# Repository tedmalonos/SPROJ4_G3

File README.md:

# **02-d plotter PCB 4-layer**
<br />
Front view<br />
<br />
Back view<br />
<br />

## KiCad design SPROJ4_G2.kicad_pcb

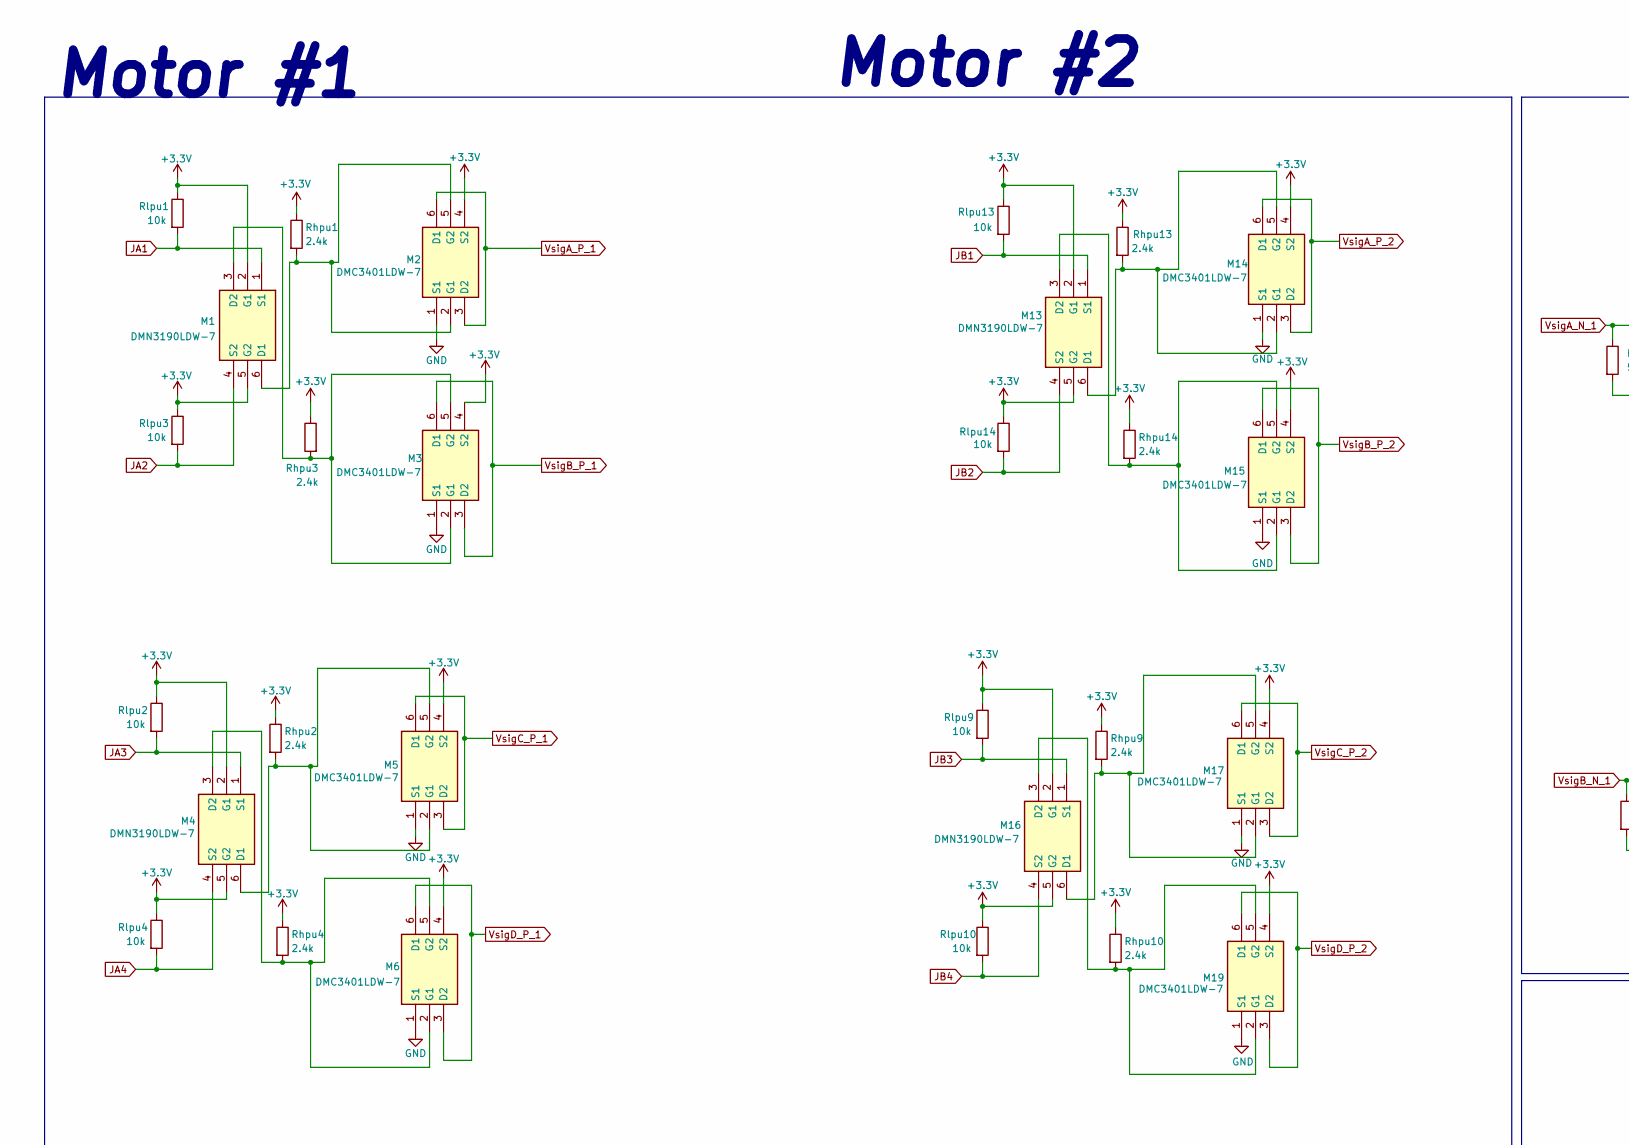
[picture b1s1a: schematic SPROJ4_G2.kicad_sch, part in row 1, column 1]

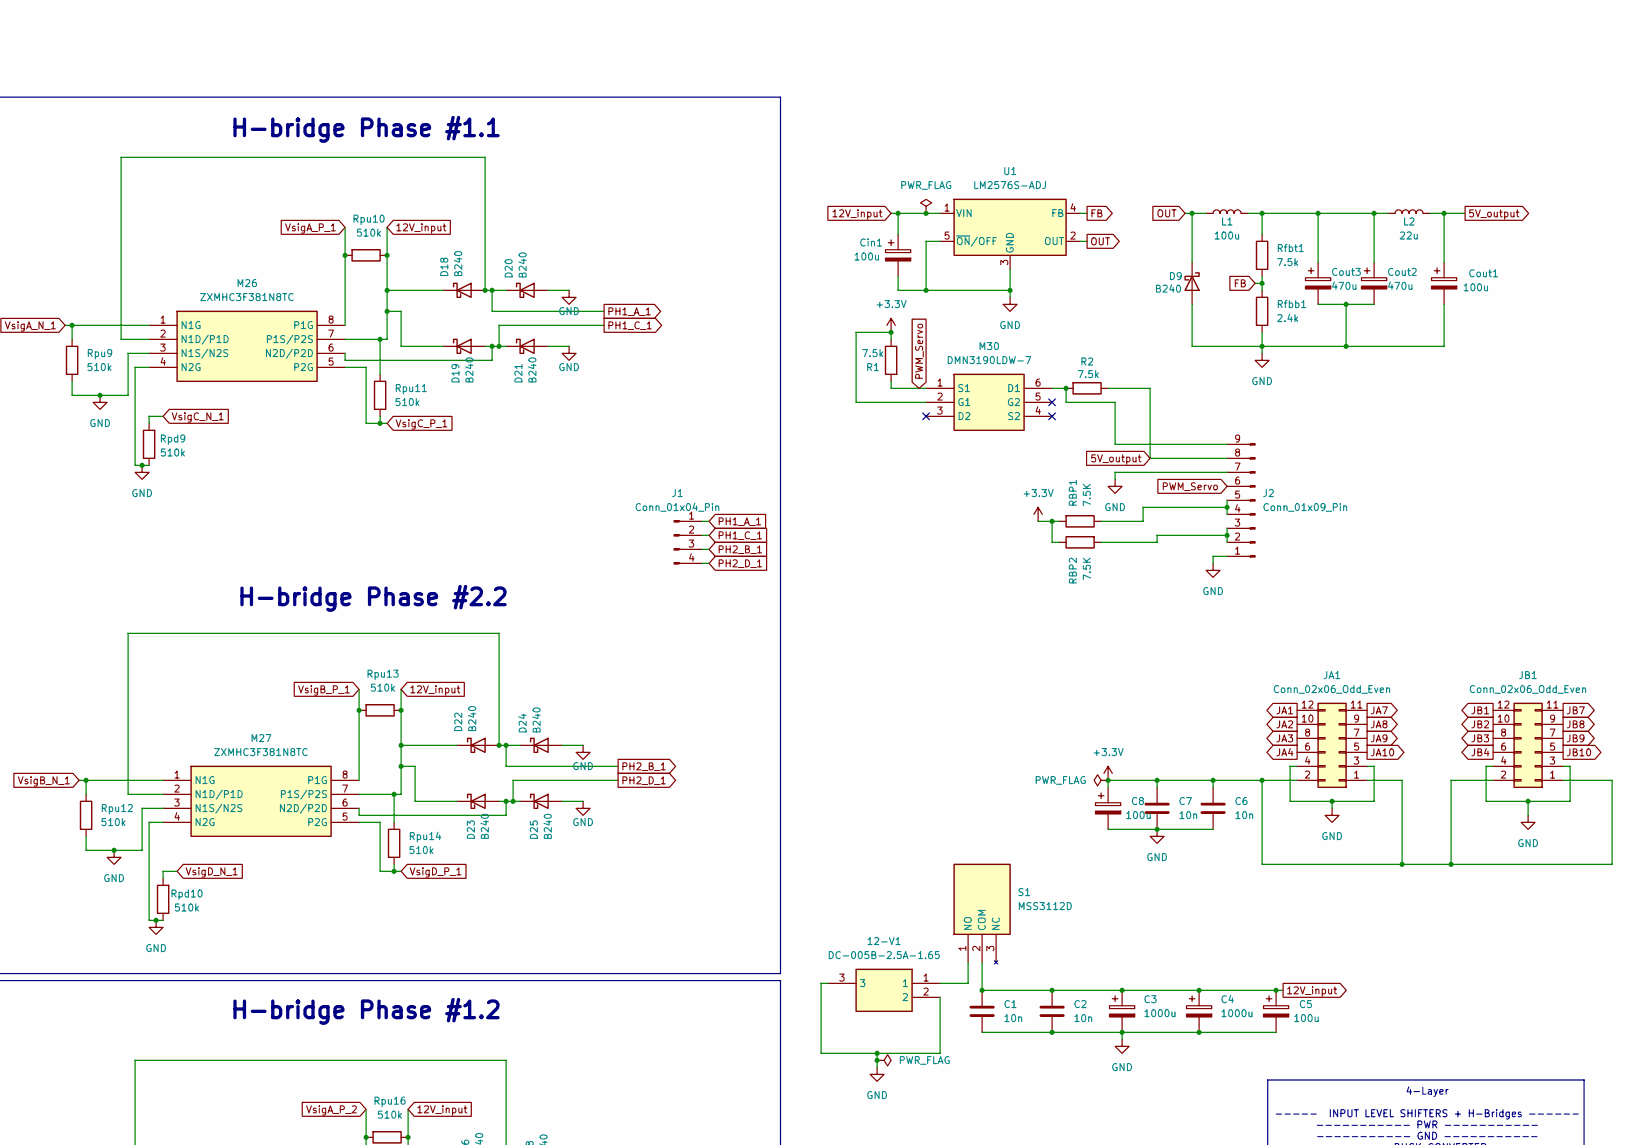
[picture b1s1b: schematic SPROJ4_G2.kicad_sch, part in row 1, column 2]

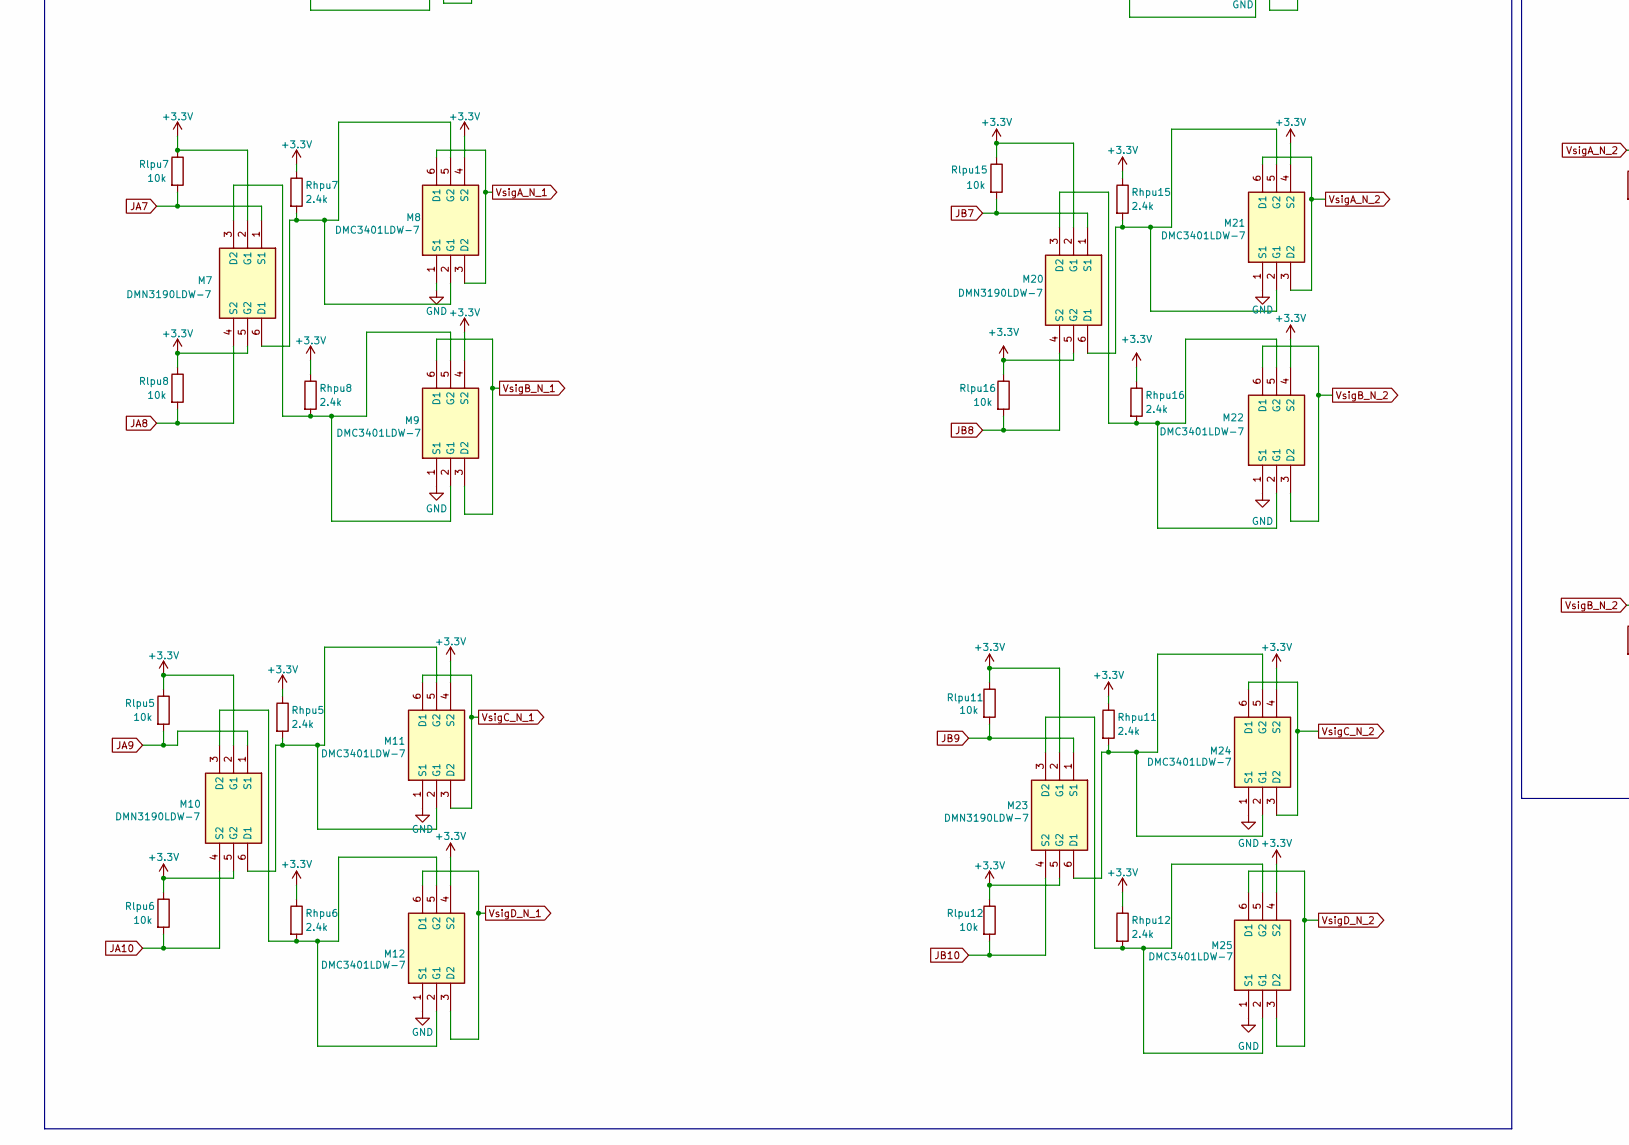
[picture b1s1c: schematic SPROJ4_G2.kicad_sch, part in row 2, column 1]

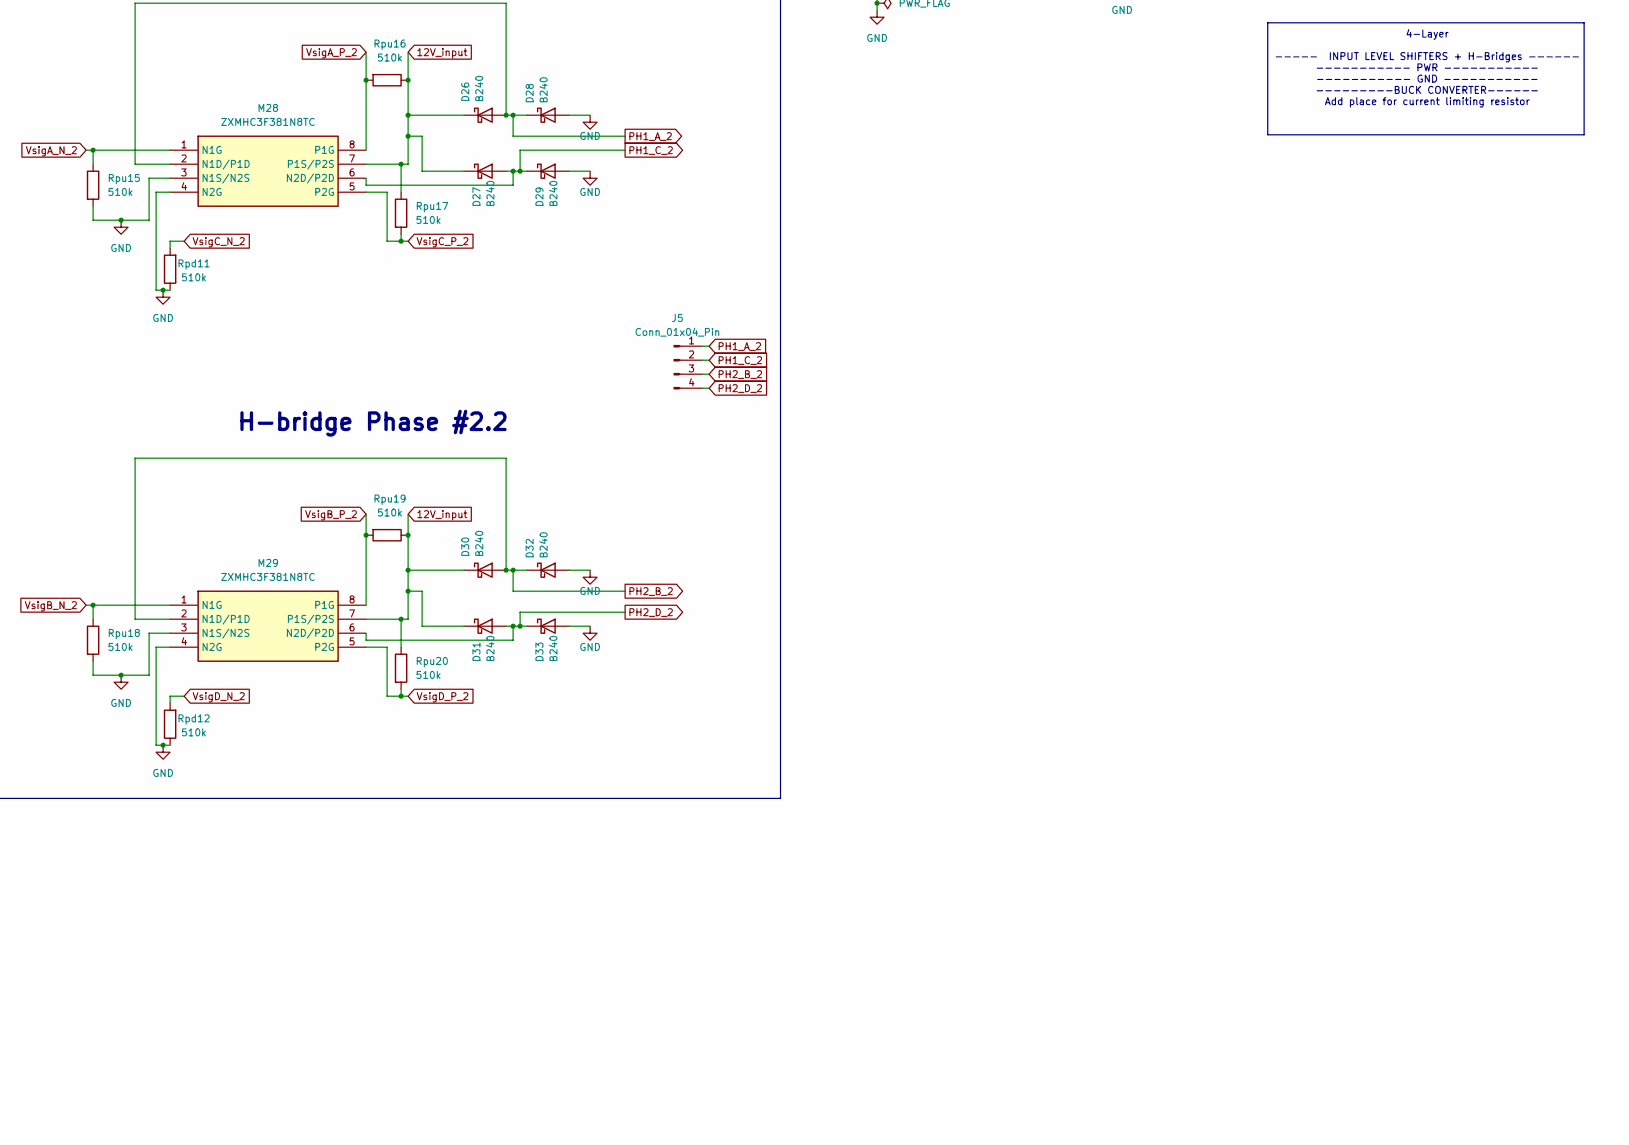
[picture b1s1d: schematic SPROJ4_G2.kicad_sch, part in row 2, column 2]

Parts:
12-V1: DC-005B-2.5A-1.65; DC005B25A165; Manufacturer_Part_Number DC-005B-2.5A-1.65
C1, C2, C6, C7: 10n; C_0805_2012Metric_Pad1.18x1.45mm_HandSolder
C3, C4: 1000u; EEE0JA152UAP_1
C5, C8: 100u; EEE1AA101SP
Cin1: 100u; EEE1AA101SP
Cout1: 100u; EEE1AA101SP
Cout2, Cout3: 470u; EEHZT1E331UP
D9: B240; D_SMA-SMB_Universal_Handsoldering
D18, D19, D20, D21, D22, D23, D24, D25, D26, D27, D28, D29, D30, D31, D32, D33: B240; D_SMB
J1, J5: Conn_01x04_Pin; JST_EH_B4B-EH-A_1x04_P2.50mm_Vertical
J2: Conn_01x09_Pin; PinHeader_1x09_P2.54mm_Horizontal
JA1: Conn_02x06_Odd_Even; PinHeader_2x06_P2.54mm_Horizontal
JB1: Conn_02x06_Odd_Even; PinHeader_2x06_P2.54mm_Horizontal
L1: 100u; SDR2207101KL
L2: 22u; L_Bourns_SRN6045TA
M1, M4, M7, M10, M13, M16, M20, M23, M30: DMN3190LDW-7; SOT65P210X110-6N; Manufacturer_Part_Number DMN3190LDW-7; Mouser Part Number 621-DMN3190LDW-7
M2, M3, M5, M6, M8, M9, M11, M12, M14, M15, M17, M19, M21, M22, M24, M25: DMC3401LDW-7; SOT65P210X110-6N; Manufacturer_Part_Number DMC3401LDW-7; Mouser Part Number 621-DMC3401LDW-7
M26, M27, M28, M29: ZXMHC3F381N8TC; SOIC127P600X170-8N; Manufacturer_Part_Number ZXMHC3F381N8TC; Mouser Part Number 522-ZXMHC3F381N8TC
R1, R2: 7.5k; R_0805_2012Metric_Pad1.20x1.40mm_HandSolder
RBP1, RBP2: 7.5K; R_0805_2012Metric_Pad1.20x1.40mm_HandSolder
Rfbb1: 2.4k; R_0805_2012Metric_Pad1.20x1.40mm_HandSolder
Rfbt1: 7.5k; R_0805_2012Metric_Pad1.20x1.40mm_HandSolder
Rhpu1, Rhpu2, Rhpu3, Rhpu4, Rhpu5, Rhpu6, Rhpu7, Rhpu8, Rhpu9, Rhpu10, Rhpu11, Rhpu12, Rhpu13, Rhpu14, Rhpu15, Rhpu16: 2.4k; R_0805_2012Metric_Pad1.20x1.40mm_HandSolder
Rlpu1, Rlpu2, Rlpu3, Rlpu4, Rlpu5, Rlpu6, Rlpu7, Rlpu8, Rlpu9, Rlpu10, Rlpu11, Rlpu12, Rlpu13, Rlpu14, Rlpu15, Rlpu16: 10k; R_0805_2012Metric_Pad1.20x1.40mm_HandSolder
Rpd9, Rpd10, Rpd11, Rpd12: 510k; R_0805_2012Metric_Pad1.20x1.40mm_HandSolder
Rpu9, Rpu10, Rpu11, Rpu12, Rpu13, Rpu14, Rpu15, Rpu16, Rpu17, Rpu18, Rpu19, Rpu20: 510k; R_0805_2012Metric_Pad1.20x1.40mm_HandSolder
S1: MSS3112D; Manufacturer_Part_Number MSS3112D
U1: LM2576S-ADJ; TO-263-5_TabPin3

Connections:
5V_output: Cout1.1, J2.8, L2.2, R2.1
12V_input: C1.1, C2.1, C3.1, C4.1, C5.1, Cin1.1, D18.1 (K), D19.1 (K), D22.1 (K), D23.1 (K), D26.1 (K), D27.1 (K), D30.1 (K), D31.1 (K), M26.7 (P1S/P2S), M27.7 (P1S/P2S), M28.7 (P1S/P2S), M29.7 (P1S/P2S), Rpu10.1, Rpu11.1, Rpu13.1, Rpu14.1, Rpu16.1, Rpu17.1, Rpu19.1, Rpu20.1, S1.2 (COM), U1.1 (VIN); also elsewhere on the board
+3.3V: C6.1, C7.1, C8.1, JA1.1, JA1.2, JB1.1, JB1.2, M1.2 (G1), M1.5 (G2), M2.4 (S2), M3.4 (S2), M4.2 (G1), M4.5 (G2), M5.4 (S2), M6.4 (S2), M7.2 (G1), M7.5 (G2), M8.4 (S2), M9.4 (S2), M10.2 (G1), M10.5 (G2), M11.4 (S2), M12.4 (S2), M13.2 (G1), M13.5 (G2), M14.4 (S2), M15.4 (S2), M16.2 (G1), M16.5 (G2), M17.4 (S2), M19.4 (S2), M20.2 (G1), M20.5 (G2), M21.4 (S2), M22.4 (S2), M23.2 (G1), M23.5 (G2), M24.4 (S2), M25.4 (S2), M30.2 (G1), R1.1, RBP1.2, RBP2.1, Rhpu1.1, Rhpu2.1, Rhpu3.1, Rhpu4.1, Rhpu5.1, Rhpu6.1, Rhpu7.1, Rhpu8.1, Rhpu9.1, Rhpu10.1, Rhpu11.1, Rhpu12.1, Rhpu13.1, Rhpu14.1, Rhpu15.1, Rhpu16.1, Rlpu1.1, Rlpu2.1, Rlpu3.1, Rlpu4.1, Rlpu5.1, Rlpu6.1, Rlpu7.1, Rlpu8.1, Rlpu9.1, Rlpu10.1, Rlpu11.1, Rlpu12.1, Rlpu13.1, Rlpu14.1, Rlpu15.1, Rlpu16.1; also elsewhere on the board
FB: Rfbb1.1, Rfbt1.2, U1.4 (FB)
GND: 12-V1.2, 12-V1.3, C1.2, C2.2, C3.2, C4.2, C5.2, C6.2, C7.2, C8.2, Cin1.2, Cout1.2, Cout2.2, Cout3.2, D9.2 (A), D20.2 (A), D21.2 (A), D24.2 (A), D25.2 (A), D28.2 (A), D29.2 (A), D32.2 (A), D33.2 (A), J2.1, J2.7, JA1.3, JA1.4, JB1.3, JB1.4, M2.1 (S1), M3.1 (S1), M5.1 (S1), M6.1 (S1), M8.1 (S1), M9.1 (S1), M11.1 (S1), M12.1 (S1), M14.1 (S1), M15.1 (S1), M17.1 (S1), M19.1 (S1), M21.1 (S1), M22.1 (S1), M24.1 (S1), M25.1 (S1), M26.3 (N1S/N2S), M26.4 (N2G), M27.3 (N1S/N2S), M27.4 (N2G), M28.3 (N1S/N2S), M28.4 (N2G), M29.3 (N1S/N2S), M29.4 (N2G), Rfbb1.2, Rpd9.1, Rpd10.1, Rpd11.1, Rpd12.1, Rpu9.2, Rpu12.2, Rpu15.2, Rpu18.2, U1.3 (GND), U1.5 (~ON/OFF); also elsewhere on the board
JA1: JA1.12, M1.1 (S1), Rlpu1.2
JA2: JA1.10, M1.4 (S2), Rlpu3.2
JA3: JA1.8, M4.1 (S1), Rlpu2.2
JA4: JA1.6, M4.4 (S2), Rlpu4.2
JA7: JA1.11, M7.1 (S1), Rlpu7.2
JA8: JA1.9, M7.4 (S2), Rlpu8.2
JA9: JA1.7, M10.1 (S1), Rlpu5.2; also elsewhere on the board
JA10: JA1.5, M10.4 (S2), Rlpu6.2
JB1: JB1.12, M13.1 (S1), Rlpu13.2
JB2: JB1.10, M13.4 (S2), Rlpu14.2; also elsewhere on the board
JB3: JB1.8, M16.1 (S1), Rlpu9.2
JB4: JB1.6, M16.4 (S2), Rlpu10.2
JB7: JB1.11, M20.1 (S1), Rlpu15.2
JB8: JB1.9, M20.4 (S2), Rlpu16.2
JB9: JB1.7, M23.1 (S1), Rlpu11.2
JB10: JB1.5, M23.4 (S2), Rlpu12.2
unnamed: Cout2.1, Cout3.1, L1.2, L2.1, Rfbt1.1
unnamed 22: J2.2, J2.3, RBP2.2; also elsewhere on the board
unnamed 23: J2.4, J2.5, RBP1.1; also elsewhere on the board
unnamed: J2.9, M30.6 (D1), R2.2
unnamed 25: M1.6 (D1), M2.2 (G1), M2.5 (G2), Rhpu1.2; also elsewhere on the board
unnamed: M1.3 (D2), M3.2 (G1), M3.5 (G2), Rhpu3.2
unnamed: M4.6 (D1), M5.2 (G1), M5.5 (G2), Rhpu2.2
unnamed: M4.3 (D2), M6.2 (G1), M6.5 (G2), Rhpu4.2
unnamed: M7.6 (D1), M8.2 (G1), M8.5 (G2), Rhpu7.2
unnamed: M7.3 (D2), M9.2 (G1), M9.5 (G2), Rhpu8.2
unnamed: M10.6 (D1), M11.2 (G1), M11.5 (G2), Rhpu5.2
unnamed 32: M10.3 (D2), M12.2 (G1), M12.5 (G2), Rhpu6.2; also elsewhere on the board
unnamed: M13.6 (D1), M14.2 (G1), M14.5 (G2), Rhpu13.2
unnamed: M13.3 (D2), M15.2 (G1), M15.5 (G2), Rhpu14.2
unnamed 35: M16.6 (D1), M17.2 (G1), M17.5 (G2), Rhpu9.2; also elsewhere on the board
unnamed 36: M16.3 (D2), M19.2 (G1), M19.5 (G2), Rhpu10.2; also elsewhere on the board
unnamed 37: M20.6 (D1), M21.2 (G1), M21.5 (G2), Rhpu15.2; also elsewhere on the board
unnamed: M20.3 (D2), M22.2 (G1), M22.5 (G2), Rhpu16.2
unnamed: M23.6 (D1), M24.2 (G1), M24.5 (G2), Rhpu11.2
unnamed: M23.3 (D2), M25.2 (G1), M25.5 (G2), Rhpu12.2
unnamed: 12-V1.1, S1.1 (NO)
OUT: D9.1 (K), L1.1, U1.2 (OUT)
PH1_A_1: D18.2 (A), D20.1 (K), J1.1, M26.2 (N1D/P1D)
PH1_A_2: D26.2 (A), D28.1 (K), J5.1, M28.2 (N1D/P1D)
PH1_C_1: D19.2 (A), D21.1 (K), J1.2, M26.6 (N2D/P2D)
PH1_C_2: D27.2 (A), D29.1 (K), J5.2, M28.6 (N2D/P2D)
PH2_B_1: D22.2 (A), D24.1 (K), J1.3, M27.2 (N1D/P1D)
PH2_B_2: D30.2 (A), D32.1 (K), J5.3, M29.2 (N1D/P1D)
PH2_D_1: D23.2 (A), D25.1 (K), J1.4, M27.6 (N2D/P2D)
PH2_D_2: D31.2 (A), D33.1 (K), J5.4, M29.6 (N2D/P2D)
PWM_Servo: J2.6, M30.1 (S1), R1.2
VsigA_N_1: M8.3 (D2), M8.6 (D1), M26.1 (N1G), Rpu9.1
VsigA_N_2: M21.3 (D2), M21.6 (D1), M28.1 (N1G), Rpu15.1
VsigA_P_1: M2.3 (D2), M2.6 (D1), M26.8 (P1G), Rpu10.2; also elsewhere on the board
VsigA_P_2: M14.3 (D2), M14.6 (D1), M28.8 (P1G), Rpu16.2
VsigB_N_1: M9.3 (D2), M9.6 (D1), M27.1 (N1G), Rpu12.1
VsigB_N_2: M22.3 (D2), M22.6 (D1), M29.1 (N1G), Rpu18.1
VsigB_P_1: M3.3 (D2), M3.6 (D1), M27.8 (P1G), Rpu13.2; also elsewhere on the board
VsigB_P_2: M15.3 (D2), M15.6 (D1), M29.8 (P1G), Rpu19.2
VsigC_N_1: M11.3 (D2), M11.6 (D1), Rpd9.2
VsigC_N_2: M24.3 (D2), M24.6 (D1), Rpd11.2
VsigC_P_1: M5.3 (D2), M5.6 (D1), M26.5 (P2G), Rpu11.2
VsigC_P_2: M17.3 (D2), M17.6 (D1), M28.5 (P2G), Rpu17.2
VsigD_N_1: M12.3 (D2), M12.6 (D1), Rpd10.2
VsigD_N_2: M25.3 (D2), M25.6 (D1), Rpd12.2
VsigD_P_1: M6.3 (D2), M6.6 (D1), M27.5 (P2G), Rpu14.2
VsigD_P_2: M19.3 (D2), M19.6 (D1), M29.5 (P2G), Rpu20.2

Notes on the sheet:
Motor #2
H-bridge Phase #2.2
H-bridge Phase #1.2
Motor #1
H-bridge Phase #1.1
4-Layer ----- INPUT LEVEL SHIFTERS + H-Bridges ------ ----------- PWR ----------- ----------- GND ----------- ---------BUCK CONVERTER------ Add place for current limiting resistor

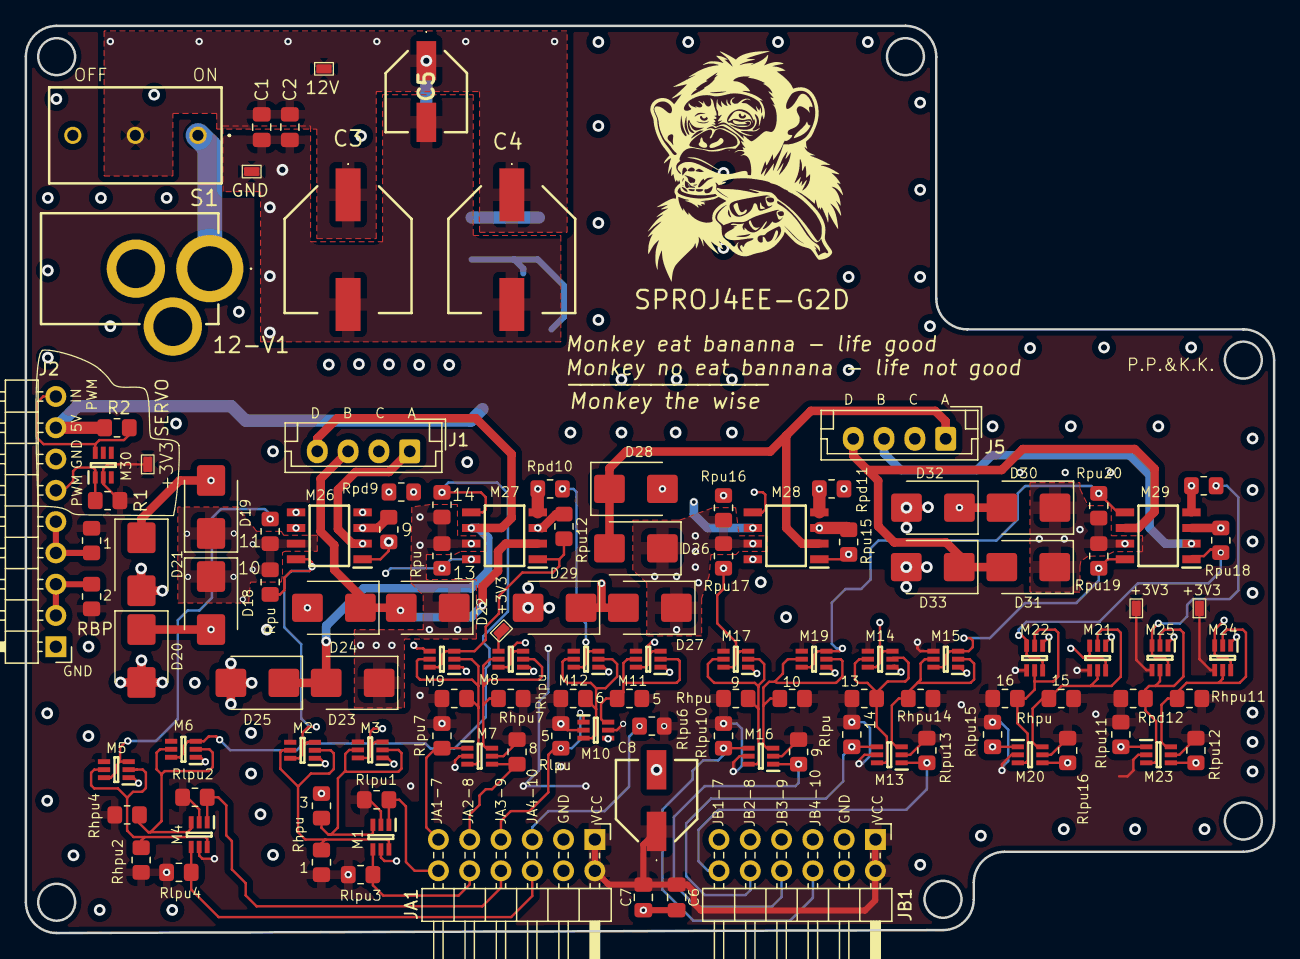
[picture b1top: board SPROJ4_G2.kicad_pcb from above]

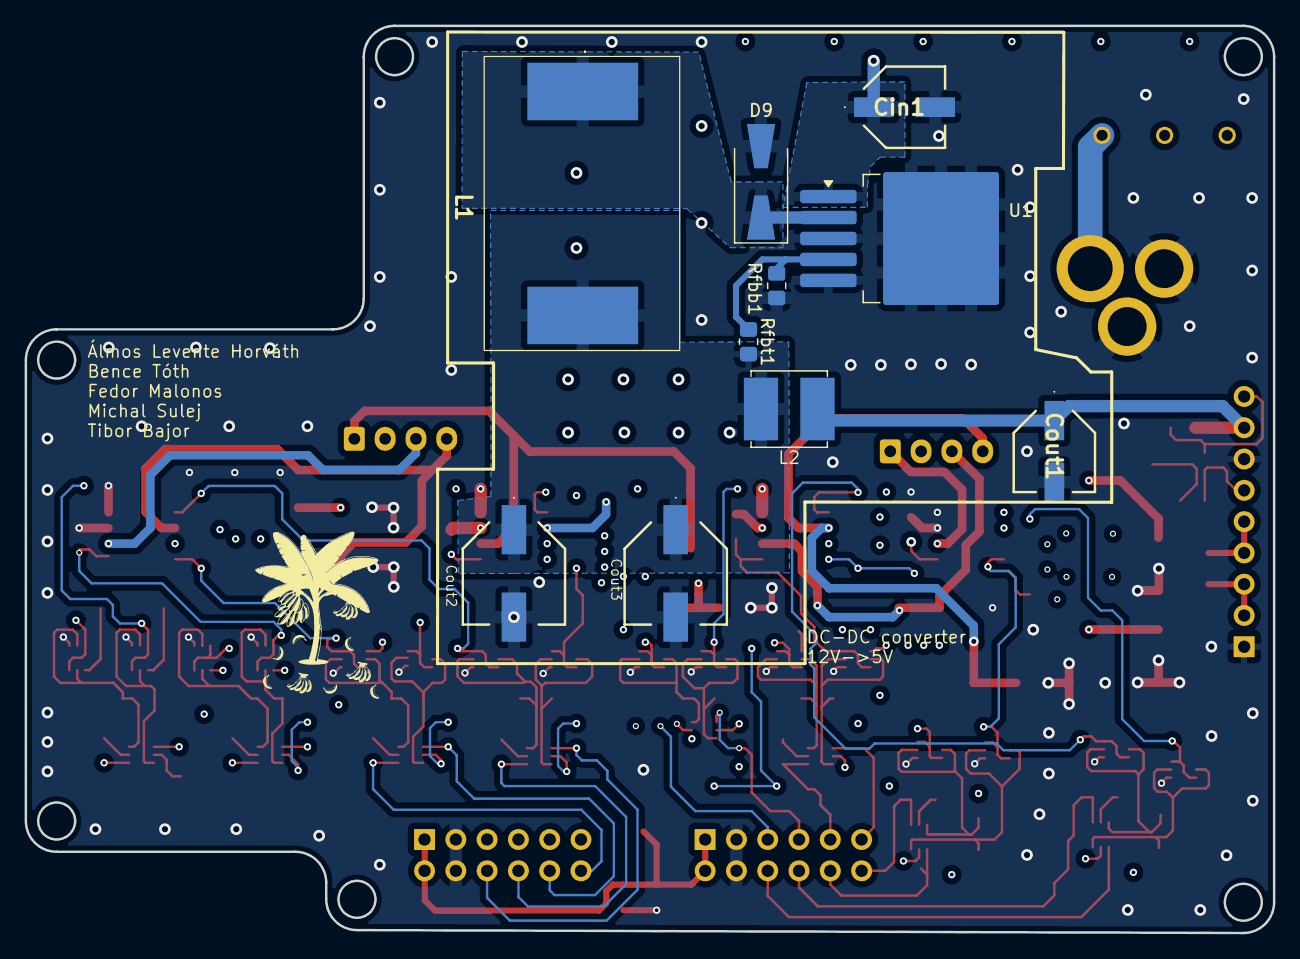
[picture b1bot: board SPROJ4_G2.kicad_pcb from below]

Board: 4 copper layers, 101.3 x 73.7 mm, 128 parts (10 on the bottom side), 68 nets.

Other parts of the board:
1: 7.5K; R_0805_2012Metric_Pad1.20x1.40mm_HandSolder
10: 2.4k; R_0805_2012Metric_Pad1.20x1.40mm_HandSolder
12V: Untitled
+3V3, +3V3#2, +3V3#3, +3V3#4: Untitled
GND: Untitled
RBP: 7.5K; R_0805_2012Metric_Pad1.20x1.40mm_HandSolder
Rhpu: 2.4k; R_0805_2012Metric_Pad1.20x1.40mm_HandSolder
Rhpu#2, Rhpu#3, Rhpu#4: 2.4k; R_0805_2012Metric_Pad1.20x1.40mm_HandSolder
Rlpu: 10k; R_0805_2012Metric_Pad1.20x1.40mm_HandSolder
Rlpu#2: 10k; R_0805_2012Metric_Pad1.20x1.40mm_HandSolder
Rpu: 510k; R_0805_2012Metric_Pad1.20x1.40mm_HandSolder
Rpu#2: 510k; R_0805_2012Metric_Pad1.20x1.40mm_HandSolder

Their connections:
12V_input: 12V.1, Rpu.1, Rpu#2.1; also elsewhere on the board
+3.3V: 1.2, 10.1, +3V3.1, +3V3#2.1, +3V3#3.1, +3V3#4.1, RBP.1, Rhpu.1, Rhpu#2.1, Rhpu#3.1, Rhpu#4.1, Rlpu.1, Rlpu#2.1; also elsewhere on the board
GND: GND.1; also elsewhere on the board
JA9: Rlpu#2.2; also elsewhere on the board
JB2: Rlpu.2; also elsewhere on the board
unnamed 22: RBP.2; also elsewhere on the board
unnamed 23: 1.1; also elsewhere on the board
unnamed 25: Rhpu#2.2; also elsewhere on the board
unnamed 32: Rhpu#4.2; also elsewhere on the board
unnamed 35: Rhpu.2; also elsewhere on the board
unnamed 36: 10.2; also elsewhere on the board
unnamed 37: Rhpu#3.2; also elsewhere on the board
VsigA_P_1: Rpu.2; also elsewhere on the board
VsigB_P_1: Rpu#2.2; also elsewhere on the board
